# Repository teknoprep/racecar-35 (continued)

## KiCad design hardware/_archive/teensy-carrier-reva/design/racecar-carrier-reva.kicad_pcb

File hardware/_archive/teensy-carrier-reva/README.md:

# Racecar-35 Teensy carrier — Rev A prototype

**UNBUILT / NOT RELEASED FOR VEHICLE USE.** This is a complete, routed **prototype
carrier PCB**, not a validated automotive ECU and not a production safety sign-off.
Start with a small prototype order only after an electronics engineer reviews the
schematic, module orientations, connector pinouts, and protection scheme. Read
[BRINGUP.md](BRINGUP.md) before connecting a Teensy or display.

## What you get

- Editable **KiCad 9** project, hierarchical schematic and local libraries in `design/`.
- `schematic.pdf`: overview + four circuit/connectivity sheets.
- `BOM.csv`: per-reference manufacturer and part number; `BOM-grouped.csv`: grouped
  purchasing list (excludes bare-PCB test pads/mounting holes); `BOM-extra.csv`: sockets,
  mating connectors, harness fuse, standoffs and externally attached modules.
- `gerbers/`: two copper layers, solder masks, silkscreens, front paste, outline,
  plated/non-plated Excellon drill files and a drill map.
- `racecar-carrier-reva-GERBERS-PROTOTYPE.zip`: bare-PCB manufacturing files only.
- `assembly-positions.csv`, `assembly-top.pdf`, `board-top.png`, `board-bottom.png`.
- `reports/`: PCB DRC, limited schematic ERC, schematic/netlist cross-check and hashes.
- `export.sh`: fail-hard verification and export; does **not** regenerate or reroute.

A PCB fabricator needs the **Gerber ZIP plus FABRICATION.md**. Gerbers alone do not
specify copper weight. A PCB assembler additionally needs the BOM, positions, PDFs,
and hand-assembly notes. This is **not** a turnkey JLCPCB/LCSC assembly order: the
Teensy, Pololu and Traco modules, sockets and some connectors may require consignment
or hand assembly. Position-file rotations must be reviewed against the assembler's
package conventions. There is no claim that every MPN is currently stocked.

## Basic design and limits

| Item | Rev A |
|---|---|
| PCB | 130 × 110 mm; 2 layers; 1.6 mm FR4; **2 oz finished copper on BOTH sides** |
| Main input | **10–20 V DC**, common negative; not an unprotected battery connection |
| Main regulator U2 | **Pololu D36V50F5, product 4091**; published 5.5–50 V input, 5 V nominal, typical 5.5 A at 36 V; this carrier budgets **5 A total** on the main 5 V rail |
| Screen branch | 5 V output, **4 A fast fuse F2**; no adjustable output voltage |
| Auxiliary regulator U3 | **Traco TSR 1-2433**, 3.3 V, nominal 1 A; Rev A peripheral budget **500 mA combined** until thermal testing |
| MCU | Socketed **Teensy 4.1**, supplied at VIN through SS14 and JP1; never externally feed its 3.3 V pins |
| Screen link | Full-duplex **5 V TTL UART**, translated to Teensy's 3.3 V logic; 921600 baud firmware |
| Screen connector | Four-position 5.08 mm screw terminal, matching functions of Advance **J10** |
| Tach | External optocoupler output -> pull-up/filter/Schmitt buffer -> **Teensy 9** |
| GPS | Four-pin JST-XH custom UART connector, **3.3 V power and logic** |
| IMU | Four-pin JST-XH, 3.3 V, I²C on Teensy 18/19 |
| Optional CAN | Connector for an **external SN65HVD230 transceiver module**; not CANH/CANL |
| Optional Ethernet | Custom 2×4 header for a **3.3 V W5500 breakout**; not a plug-compatible W5500 footprint |

The regulator's published current is not a guarantee of **continuous 5 A in your
closed, hot trunk enclosure**. Verify at 10, 14.4 and 20 V, maximum brightness/radio
activity, and maximum intended ambient. Fuse values are not precise current limits.
The screen is not forced to draw 4 A or 5 A; it draws its own load current.
The screen fuse leaves margin for the MCU. U3 is fed separately from the protected
input, so its output is not drawn through the Teensy's small 3.3 V regulator.

This first PCB deliberately uses an **assembled regulator module** instead of a
new discrete 25 W buck-converter design. U2 mounts above the carrier on a soldered
2×6 header. That makes the power design easier to build and review; it is not the
cheapest possible mass-production implementation.

### Not included

GPS receiver/antenna, MPU-6050, CAN transceiver and W5500 are external modules.
There is **no** SMA connector or GNSS chip on this carrier: the SMA stays on the GPS
breakout, away from switching regulators. The Teensy's own SD slot is used. No raw
coil/ignition input, no direct 12 V tach, and **no oil-pressure/NTC conditioning** are
implemented. Firmware ADC readings must not be trusted without the existing proper
external conditioning; pins 16/17 are not brought to sensor screw terminals here.

There is no firmware change, GPS-module auto-detection, or M10/F10 library migration
in this PCB package. The current firmware's tested target remains NEO-M9N.
**A compatible UART voltage does not imply software compatibility with every u-blox
generation.** Verify the exact GPS board and library support before purchasing.

## Power protection — what it does and does not do

```
J1 +10–20V -> F1 5A -> VIN_FUSED -> U2 VIN -> U2 reverse protection -> buck -> +5V_MAIN
                          |                       |
                     SMBJ20CA D1             U2 VRP -> U3 -> +3V3_AUX
                          |                                       (GPS/IMU/modules)
                         GND
+5V_MAIN -> F2 4A -> +5V_SCREEN -> J2 pin 2 and UART cable-side supplies
+5V_MAIN -> D2 SS14 -> JP1 -> Teensy VIN
Teensy 3V3 -> +3V3_MCU -> low-current logic buffers only
```

- U2 includes reverse-input protection (published up to 40 V reverse), current/short
  protection and thermal shutdown. U3 takes **VRP**, after U2's reverse protection,
  not the unprotected input. U2's EN/PG are unused; VRP must not be confused with VIN.
- D1 is **SMBJ20CA, bidirectional**, after F1. Its 20 V standoff and approximately
  32.4 V clamp at rated pulse current fit the nominal 10–20 V design. This does NOT
  establish an automotive transient rating: pulse energy, source impedance, wiring
  inductance and actual clamp voltage matter. The Traco input max is 36 V.
- **Not qualified for ISO 7637 or ISO 16750 load dump, jump-start or cranking.** Use a
  properly protected vehicle DC feed. Add a real surge-stopper/automotive front-end
  after reviewing the vehicle supply requirements, before permanent installation.
- Fit an **external 5 A harness fuse near the battery/source**. F1 only protects
  downstream of this board's input; it cannot protect the cable before the PCB.
- **Fuses do not protect a GPIO against a 5 V/12 V mistake**, and neither a fuse nor
  a current-limited supply guarantees a semiconductor will survive a fault.
- D2 blocks USB-powered Teensy VIN from feeding back into the carrier 5 V bus. It
  does **not** block carrier power from entering the computer through an intact
  Teensy VUSB/VIN bridge. **CUT THAT BRIDGE before simultaneous USB/carrier power.**
- JP1 is an initial bring-up isolation jumper, not a hot-switching control. Do not
  energize external sensors while a connected Teensy is unpowered: GPIO protection
  paths or pull-ups can phantom-power it. Make all wiring changes with all power off.
- The two 3.3 V rails must remain separate. Do not bridge AUX 3V3 to Teensy 3V3.

## Connector pinout — top view, square pad is pin 1

The words RX/TX on the carrier refer to the **Teensy/carrier**, not the screen.
Do not guess orientation from wire colours or a vendor's cable plug.

### J1 — 10–20 V input, Phoenix MKDS 1,5/2-5,08

1. Positive input, 10–20 V.
2. GND / negative return.

### J2 — SCREEN, Phoenix MKDS 1,5/4-5,08

| Pin | Carrier function | Connect to CrowPanel Advance |
|---|---|---|
| 1 | GND | J10 GND |
| 2 | **+5 V OUTPUT**, fused 4 A | J10 **+5V_IN** |
| 3 | RX: receives screen data, 5 V side | J10 **TXD0_H** |
| 4 | TX: transmits to screen, 5 V side | J10 **RXD0_H** |

**Use the larger XH2.54 / J10 power-capable header on the genuine Advance. NEVER
connect pin 2 to the small HY2.0 / J2 `3V3_OUT` header.** A clone's connector labels,
pin order and circuitry must be checked against its schematic and measured with a
meter first; its USB identity cannot establish its power-header pinout. Do not use
a same-looking cable without a pin-to-pin continuity test.

U4 is SN74LVC1T45: A=3.3 V Teensy TX, B=5 V cable TX, DIR high.
U5 reverses direction: B=5 V cable RX, A=3.3 V Teensy RX, DIR low.
Both support power-off isolation; their cable-side supply is after the screen fuse.
100 Ω series resistors and PESD5V0S1BA ESD clamps are fitted at the cable paths.
They are **not RS-232 converters** and not a 12 V miswire-protection system.

### J3 — external optocoupler, two-position screw terminal

1. GND, optocoupler output-side emitter/ground.
2. Optocoupler collector/output signal; goes to **Teensy pin 9 through U6**.

Default: **open collector**, with R6 4.7 kΩ pull-up to MCU 3.3 V. R5=1 kΩ and
C11=1 nF form a small input filter; U6 gives a 3.3 V Schmitt output. No extra onboard
opto is included. For a verified push-pull 3.3/5 V source, review/remove R6 so the
external source cannot feed the MCU supply through the pull-up, especially when
the carrier is off. Do not connect an independently powered tach module without
checking its output topology. Never attach a coil or 12 V tach signal directly.

### J4 — GPS, JST B4B-XH-A (2.50 mm)

1. +3V3_AUX **output**.
2. GND.
3. Carrier TX (Teensy 8, via R8) -> GPS RX.
4. Carrier RX (U6 input, Teensy 7) <- GPS TX.

This is a **custom harness**, not a GPS vendor standard. Choose a breakout whose
specified supply pin accepts 3.3 V. A board that requires 5 V into an onboard
regulator is not powered correctly by blindly connecting J4 pin 1 to its VIN.
Do not connect USB to the GPS while it is powered/connected here unless its vendor
explicitly permits those supply combinations and its USB-UART interface is isolated.
GPS firmware configuration and antenna requirements remain module-specific.

### J5 — IMU, JST-XH

1. +3V3_AUX; 2. GND; 3. SDA (Teensy 18); 4. SCL (Teensy 19).
MPU-6050 AD0 -> GND. R12/R13 are 4.7 kΩ I²C pull-ups; account for parallel pull-ups
already on the breakout. Keep I²C wires short. Do not allow pull-ups to 5 V.

### J6 — CAN transceiver module LOGIC, JST-XH

1. +3V3_AUX; 2. GND; 3. Teensy 22 TX -> module CTX/D; 4. Teensy 23 RX <- module CRX/R.
Use a 3.3 V **SN65HVD230** module. CANH/CANL are on that external module, not J6.
CAN termination: only at the two physical bus ends; include existing module resistors
when checking resistance. A powered-off correctly terminated bus is typically ~60 Ω
across CANH/CANL. No transceiver or terminator is fitted on this carrier.

### J7 — optional W5500, 2×4, 2.54 mm

| Pin | Function | Pin | Function |
|---|---|---|---|
| 1 | +3V3_AUX | 2 | GND |
| 3 | CS, Teensy 10 | 4 | MOSI, Teensy 11 |
| 5 | MISO, Teensy 12 | 6 | SCK, Teensy 13 |
| 7 | RESET, Teensy 6 | 8 | INT, Teensy 5 |

Custom wiring only; most W5500 modules have a different pin order. Must be powered
from 3.3 V at the specified input and use 3.3 V I/O. R10 pulls CS high and R11 pulls
RESET high. INT/RESET are wired for future use; current firmware does not promise
those optional GPIO functions are implemented. Keep SPI short and bench-test at
the firmware's clock rate. All external module current counts against the AUX budget.

## Cable reality

A four-terminal connector does not make trunk-length TTL UART noise-immune.
**Rev A has not been verified across the car at 921600 baud.** Test under engine,
alternator and radio activity with error/retry counts and a scope. If it is not
reliable, use differential transceivers at **both ends**; that needs a screen-side
adapter and potentially protocol/wiring changes, not just a different cable.

For power, calculate the **round-trip** drop. Example at 3 m one-way / 4 A:
- 18 AWG copper: approximately 0.50 V drop before connectors/fuses/temperature.
- 16 AWG: approximately 0.32 V.
- 14 AWG: approximately 0.20 V.

Select wire by measured screen current and allowable drop; don't assume a thin
four-core serial cable can carry 4–5 A. The screen's input diode adds more loss.
Use strain relief and ferrules compatible with the screw terminals, not loose
solder-tinned stranded wire under screws. A harness can have heavy power conductors
plus separately shielded/twisted signal/ground pairs while terminating at four
functions. Do not tie a shield to positive power. For now, begin with short bench
wires and measure voltage **at the screen** at maximum load.

## Verification performed and limits

`export.sh` requires:
1. KiCad PCB DRC: **zero violations, zero unconnected items**.
2. Schematic ERC: no violations. **Symbols are pin-labelled passive connectivity
   blocks**, so this ERC does not verify driver conflicts, supply sequencing or
   semiconductor voltage/current limits. Do not treat it as full electrical validation.
3. Independent assertions for key pin maps, power separation, polarity and fixed
   translator direction. Exported schematic netlist must match all 161 connected
   PCB pads from `components.json`.
4. Wide manually routed power trunks survive routing. No high-current trunk uses
   a single signal via. Ground uses wide back-layer trunks and pours on both sides.

Not done: independent engineer review, physical footprint fit, board fabrication,
measured regulator startup/ripple/fault response, thermal load testing, sustained
5 A testing, EMI, automotive transients, enclosure fit or long-cable UART tests.
These are release blockers for permanent vehicle use. Current capability cannot be
proven by Gerbers or DRC alone. Replacement modules must match the exact footprints.

## Rebuilding / editing

Tools used: KiCad 9.0.8, Python `pcbnew` from the system KiCad package, Freerouting
1.9.0 / Java 17 (under Xvfb), and CairoSVG for previews. Libraries are project-local.
Firmware builds, binaries and frozen OTA bridge are untouched.

**`generate.py` overwrites the routed PCB.** To intentionally regenerate:

```sh
/usr/bin/python3 generate.py
/usr/bin/python3 schematic.py
# Run in a scratch directory so Freerouting logs don't enter the repo:
xvfb-run -a java -jar /path/to/freerouting-1.9.0.jar \
  -de /absolute/path/design/racecar-carrier-reva.dsn \
  -do /absolute/path/design/racecar-carrier-reva.ses -mp 12 -mt 1 -da
/usr/bin/python3 finish_board.py
./export.sh
```

Delete the prior `.ses` before a new routing run so failure cannot reuse stale routes.
Source and routed `.dsn/.ses` are retained. Alternatively edit the final KiCad files
in the GUI, then update the generated source/manifest or stop using generation; never
silently overwrite manual edits. `export.sh` exports the existing final board only.

## Reference sources

- PJRC Teensy 4.1 pinout: https://www.pjrc.com/teensy/card11a_rev4_web.pdf
- Pololu module, current curves and connection diagrams: https://www.pololu.com/product/4091
- Traco TSR 1 datasheet: https://www.tracopower.com/products/tsr1.pdf
- TI translator: https://www.ti.com/lit/ds/symlink/sn74lvc1t45.pdf
- TI Schmitt buffer: https://www.ti.com/lit/ds/symlink/sn74lvc2g17.pdf
- `references/` contains the retrieved PJRC card and Pololu diagrams. Pololu's
  dimension picture is a **BOTTOM** view; the labelled power-pin picture is **TOP**.
- Stock footprint geometry: KiCad 9 footprint library, copied into `design/Racecar.pretty`.

Manufacturer documents govern. Some supplier sites could not be fetched from this
host; part selection and the current stock library are not a substitute for reviewing
the latest purchased-part datasheets before placement of an assembly order.

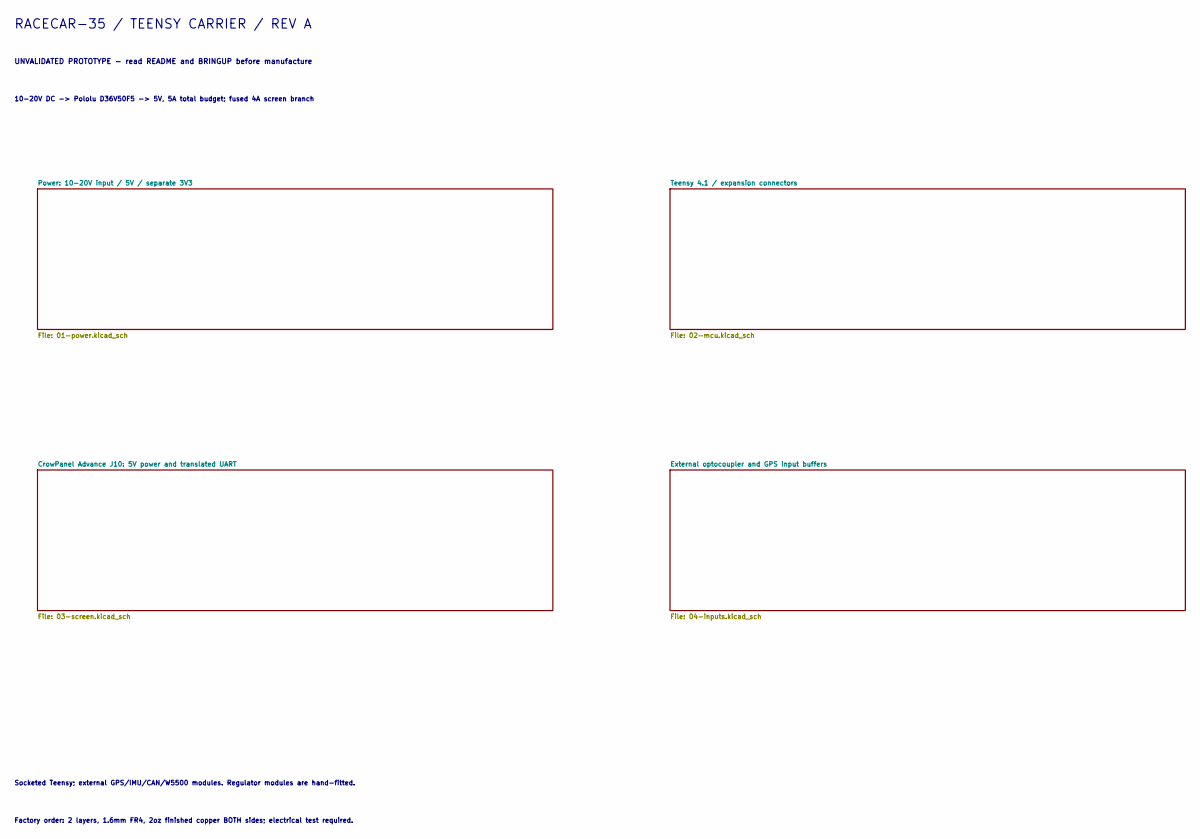
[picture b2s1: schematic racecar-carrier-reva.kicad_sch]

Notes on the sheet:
RACECAR-35 / TEENSY CARRIER / REV A
UNVALIDATED PROTOTYPE - read README and BRINGUP before manufacture
10-20V DC -> Pololu D36V50F5 -> 5V, 5A total budget; fused 4A screen branch
Socketed Teensy; external GPS/IMU/CAN/W5500 modules. Regulator modules are hand-fitted.
Factory order: 2 layers, 1.6mm FR4, 2oz finished copper BOTH sides; electrical test required.

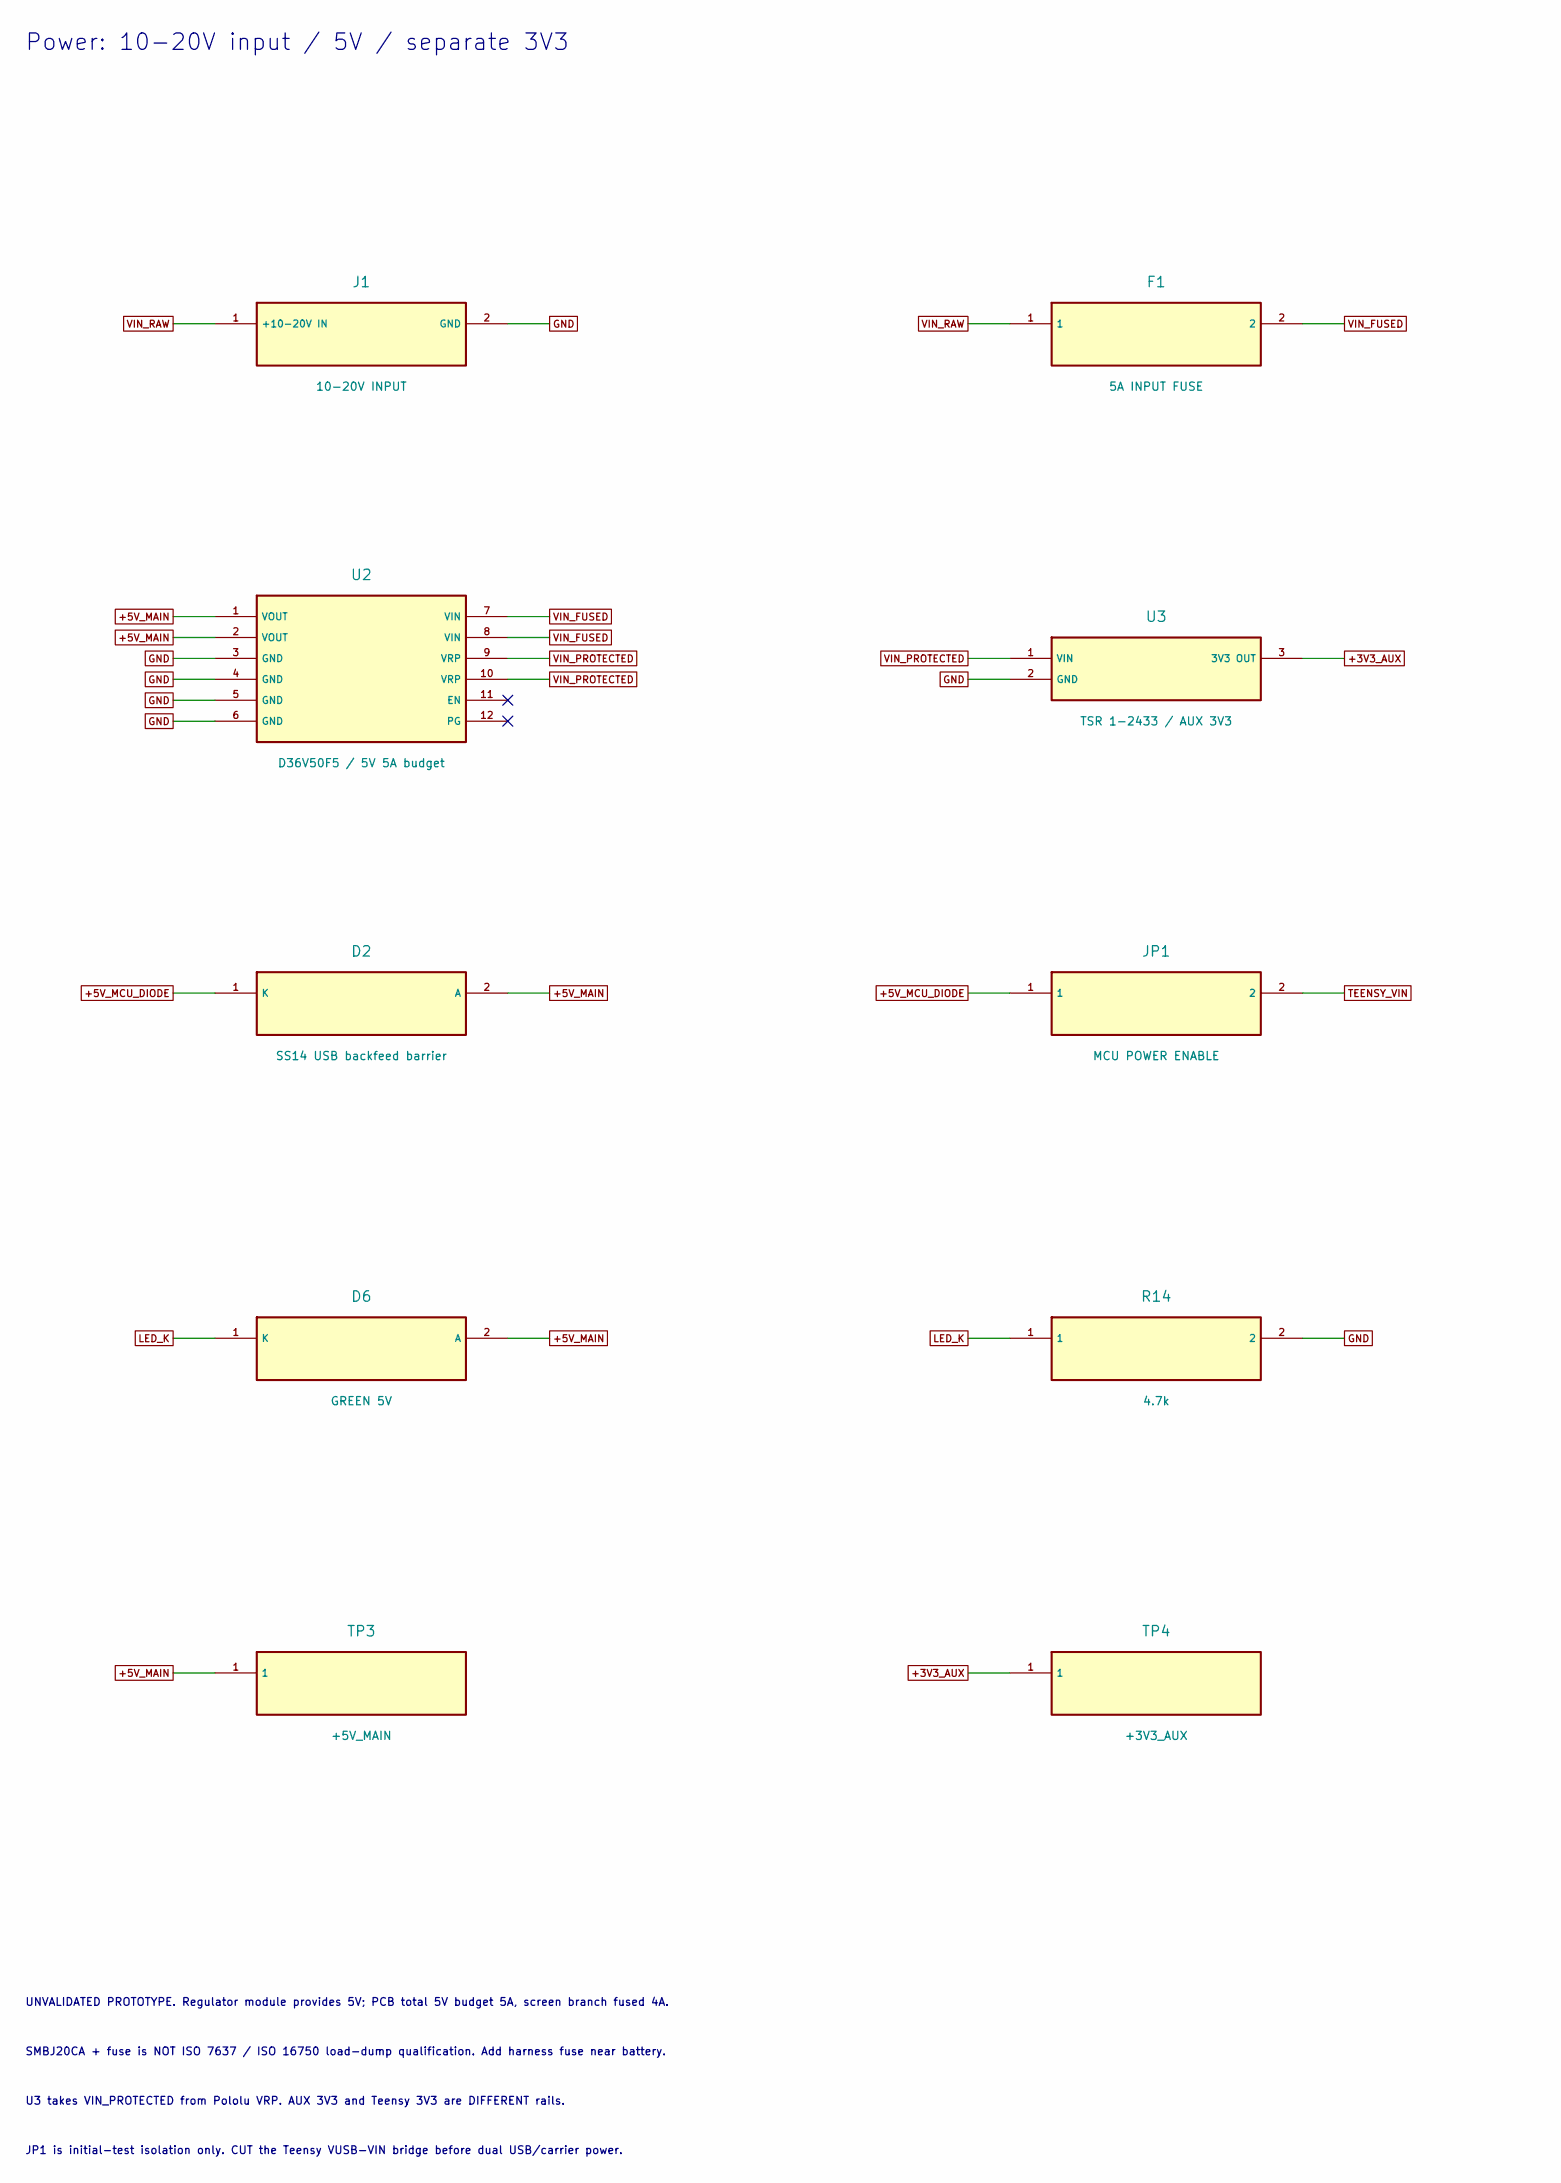
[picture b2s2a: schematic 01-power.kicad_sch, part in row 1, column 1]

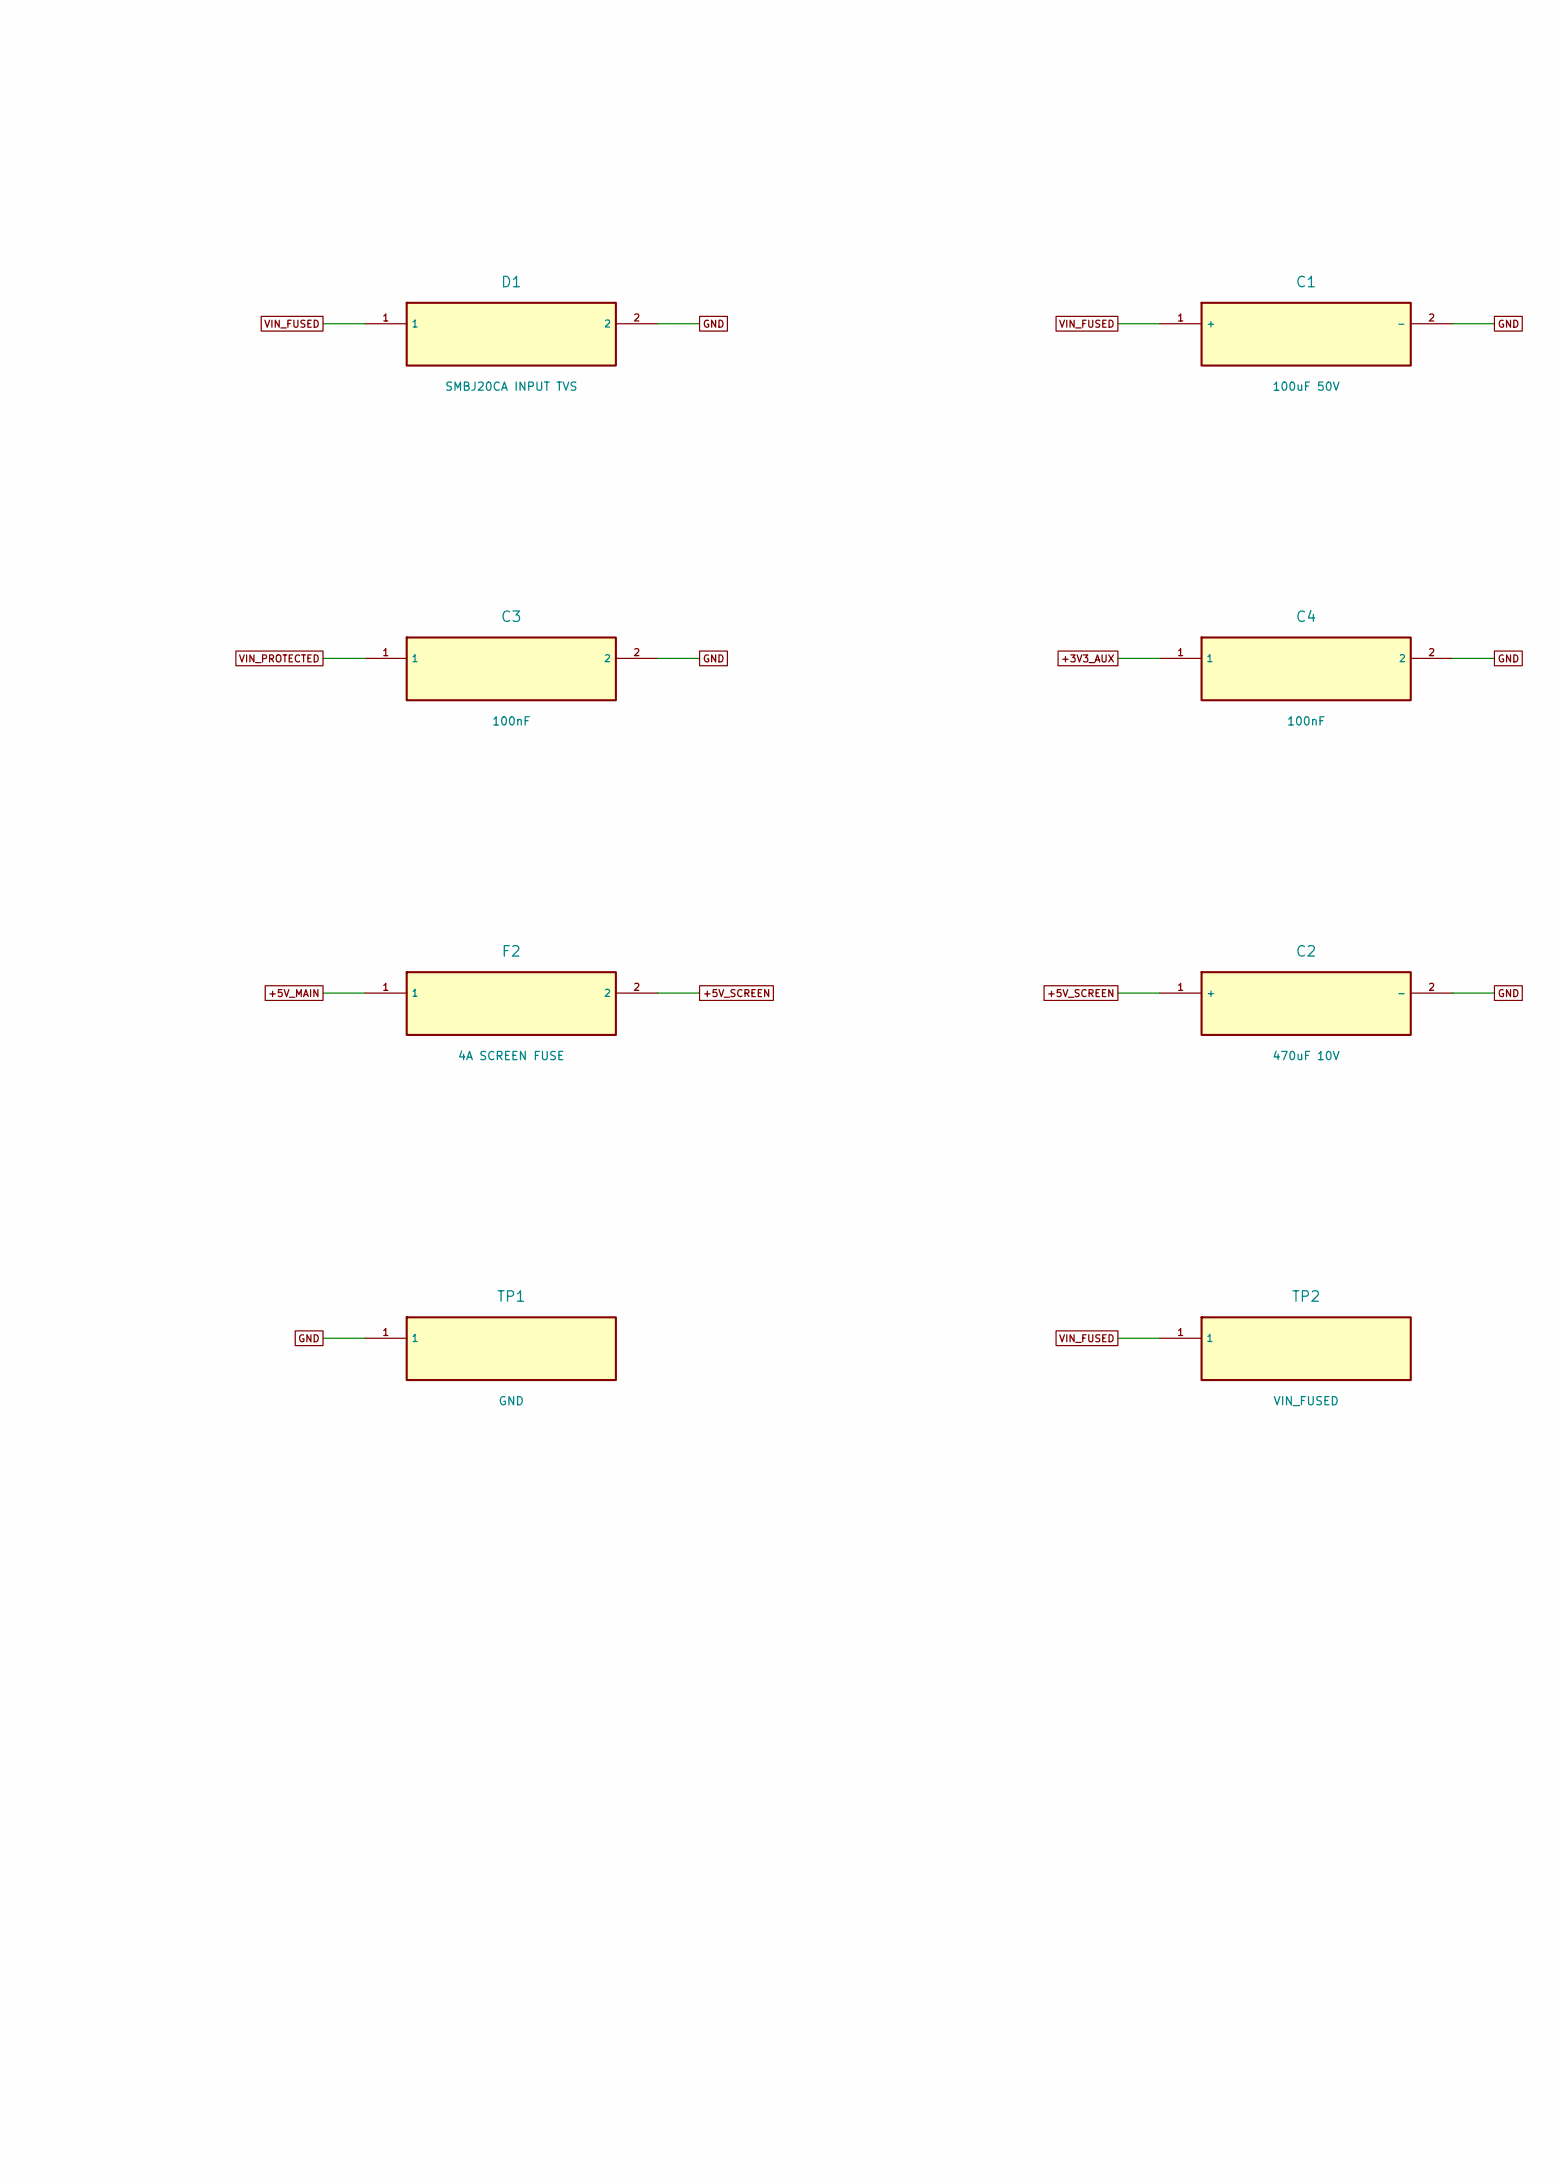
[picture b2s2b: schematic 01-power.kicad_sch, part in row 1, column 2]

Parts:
C1: 100uF 50V; CP_Radial_D8.0mm_P3.50mm
C2: 470uF 10V; CP_Radial_D8.0mm_P3.50mm
C3, C4: 100nF; C_0805_2012Metric_Pad1.18x1.45mm_HandSolder
D1: SMBJ20CA INPUT TVS; D_SMB
D2: SS14 USB backfeed barrier; D_SMA
D6: GREEN 5V; LED_0805_2012Metric
F1: 5A INPUT FUSE; Fuse_Littelfuse-NANO2-451_453
F2: 4A SCREEN FUSE; Fuse_Littelfuse-NANO2-451_453
J1: 10-20V INPUT; TerminalBlock_Phoenix_MKDS-1,5-2-5.08_1x02_P5.08mm_Horizont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
JP1: MCU POWER ENABLE; PinHeader_1x02_P2.54mm_Vertical
R14: 4.7k; R_0805_2012Metric_Pad1.20x1.40mm_HandSolder
TP1: GND; TestPoint_THTPad_D2.0mm_Drill1.0mm
TP2: VIN_FUSED; TestPoint_THTPad_D2.0mm_Drill1.0mm
TP3: +5V_MAIN; TestPoint_THTPad_D2.0mm_Drill1.0mm
TP4: +3V3_AUX; TestPoint_THTPad_D2.0mm_Drill1.0mm
U2: D36V50F5 / 5V 5A budget; Pololu_D36V50F5
U3: TSR 1-2433 / AUX 3V3; Converter_DCDC_TRACO_TSR-1_THT

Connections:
+3V3_AUX: C4.1, TP4.1, U3.3 (3V3 OUT); also elsewhere on the board
+5V_MAIN: D2.2 (A), D6.2 (A), F2.1, TP3.1, U2.1 (VOUT), U2.2 (VOUT)
+5V_MCU_DIODE: D2.1 (K), JP1.1
+5V_SCREEN: C2.1 (+), F2.2; also elsewhere on the board
GND: C1.2 (-), C2.2 (-), C3.2, C4.2, D1.2, J1.2 (GND), R14.2, TP1.1, U2.3 (GND), U2.4 (GND), U2.5 (GND), U2.6 (GND), U3.2 (GND); also elsewhere on the board
LED_K: D6.1 (K), R14.1
TEENSY_VIN: JP1.2; also elsewhere on the board
VIN_FUSED: C1.1 (+), D1.1, F1.2, TP2.1, U2.7 (VIN), U2.8 (VIN)
VIN_PROTECTED: C3.1, U2.9 (VRP), U2.10 (VRP), U3.1 (VIN)
VIN_RAW: F1.1, J1.1 (+10-20V IN)

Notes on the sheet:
Power: 10-20V input / 5V / separate 3V3
UNVALIDATED PROTOTYPE. Regulator module provides 5V; PCB total 5V budget 5A, screen branch fused 4A.
SMBJ20CA + fuse is NOT ISO 7637 / ISO 16750 load-dump qualification. Add harness fuse near battery.
U3 takes VIN_PROTECTED from Pololu VRP. AUX 3V3 and Teensy 3V3 are DIFFERENT rails.
JP1 is initial-test isolation only. CUT the Teensy VUSB-VIN bridge before dual USB/carrier power.

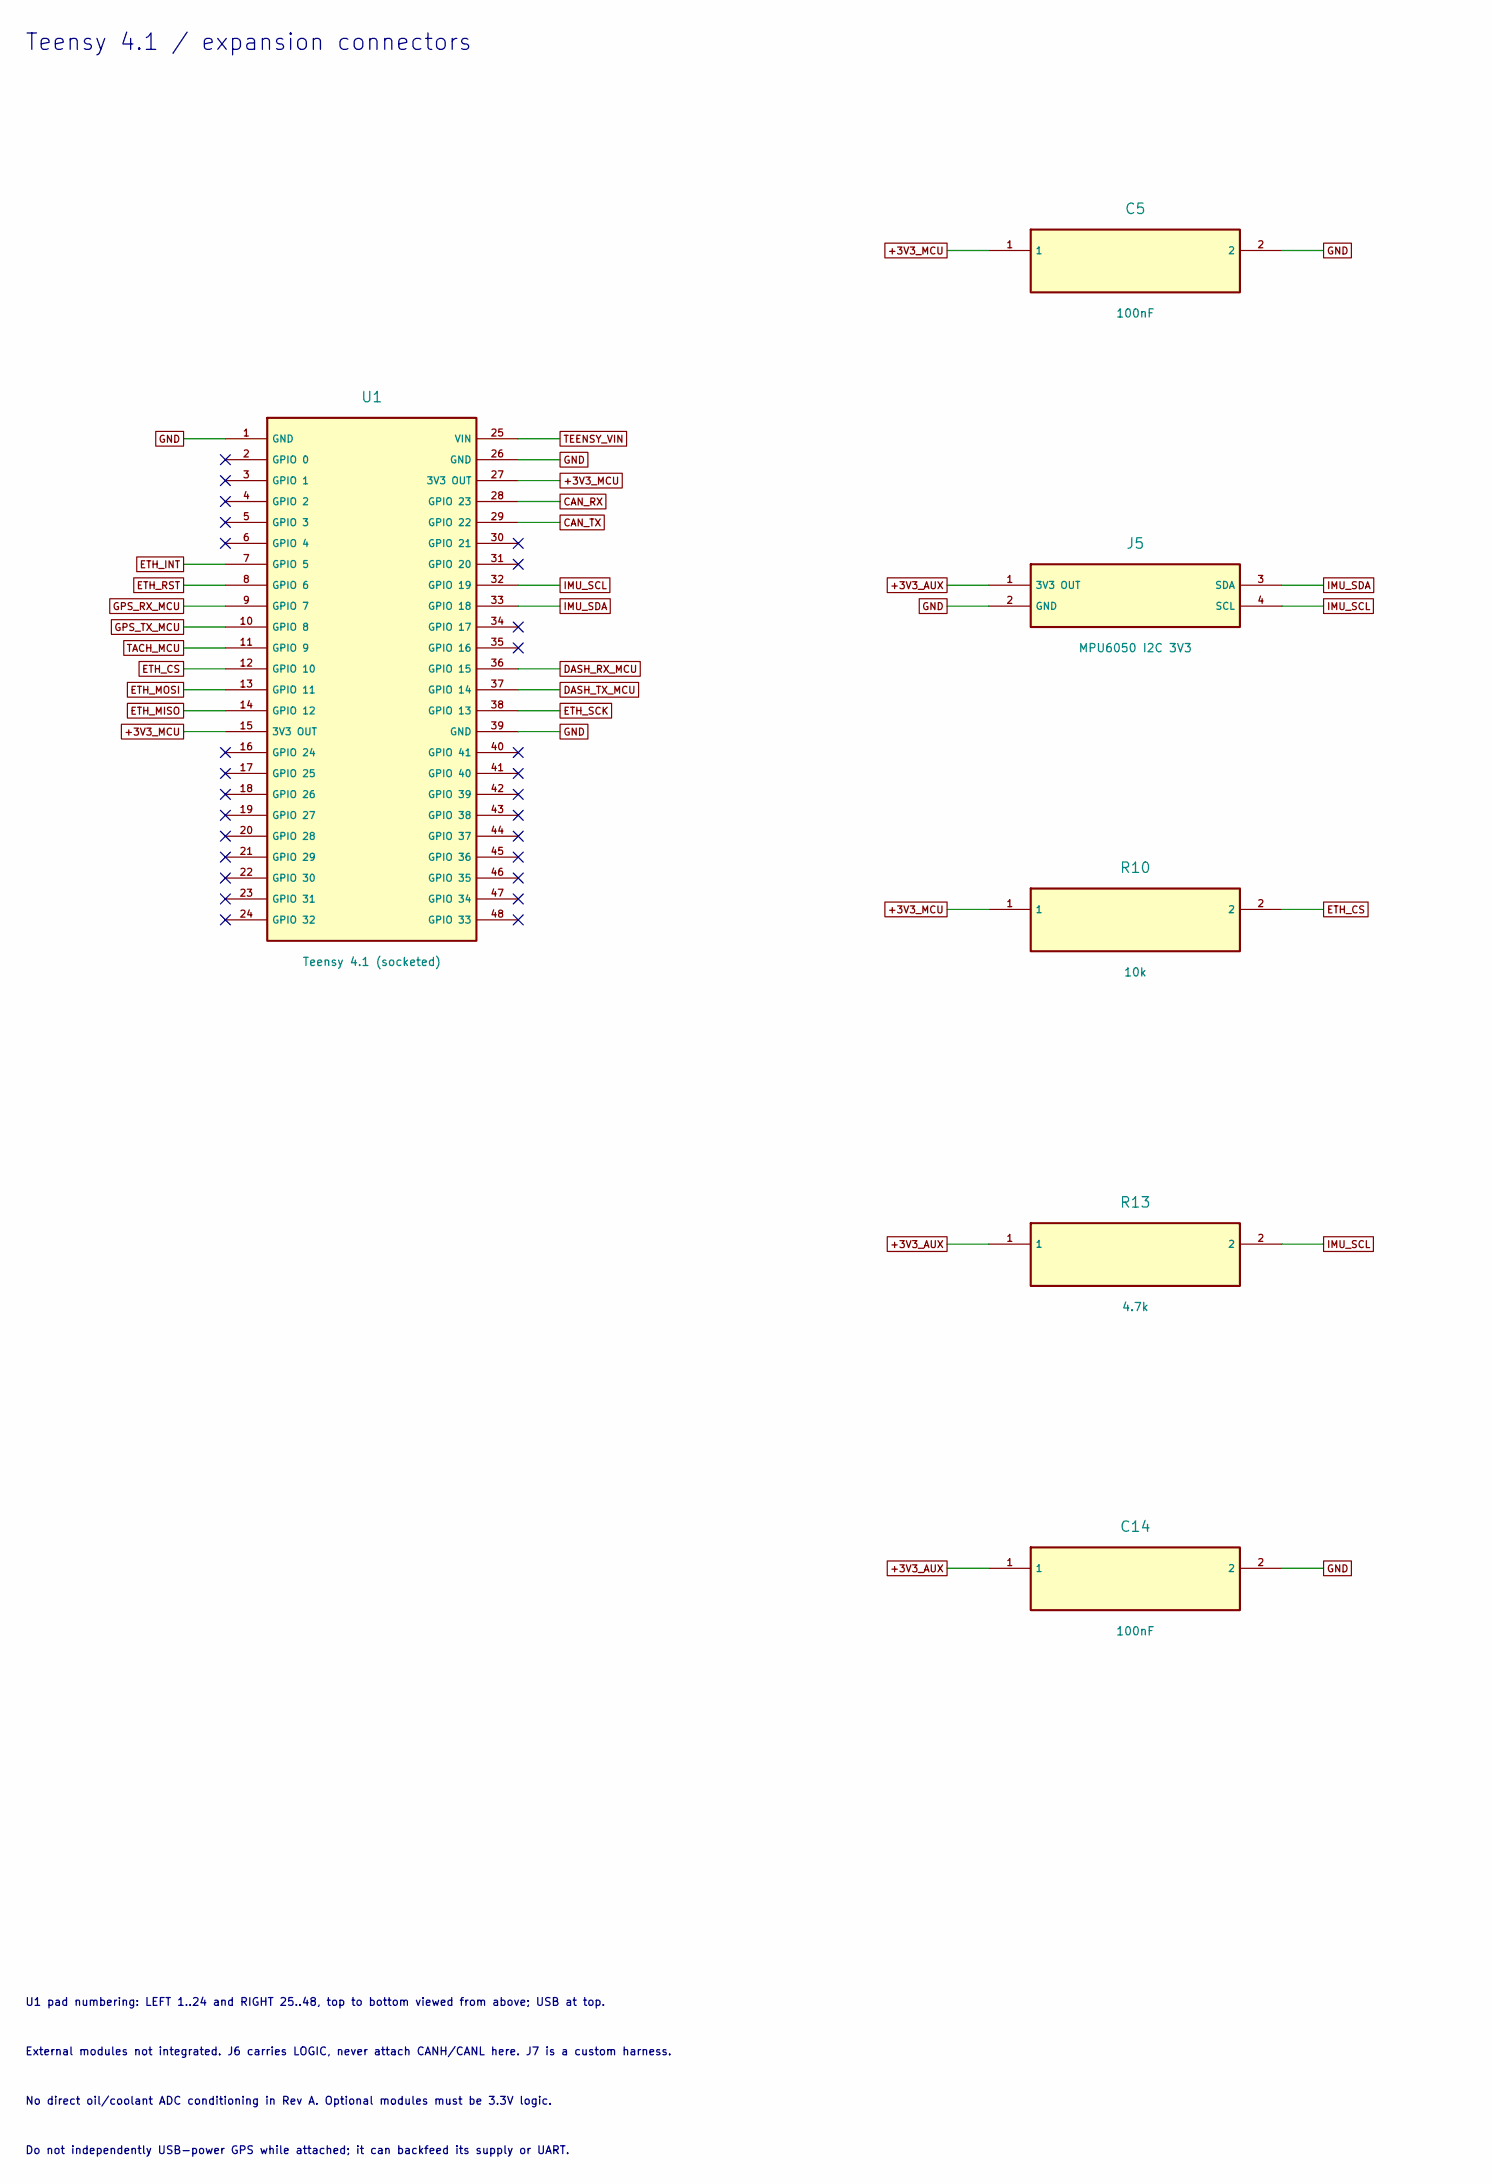
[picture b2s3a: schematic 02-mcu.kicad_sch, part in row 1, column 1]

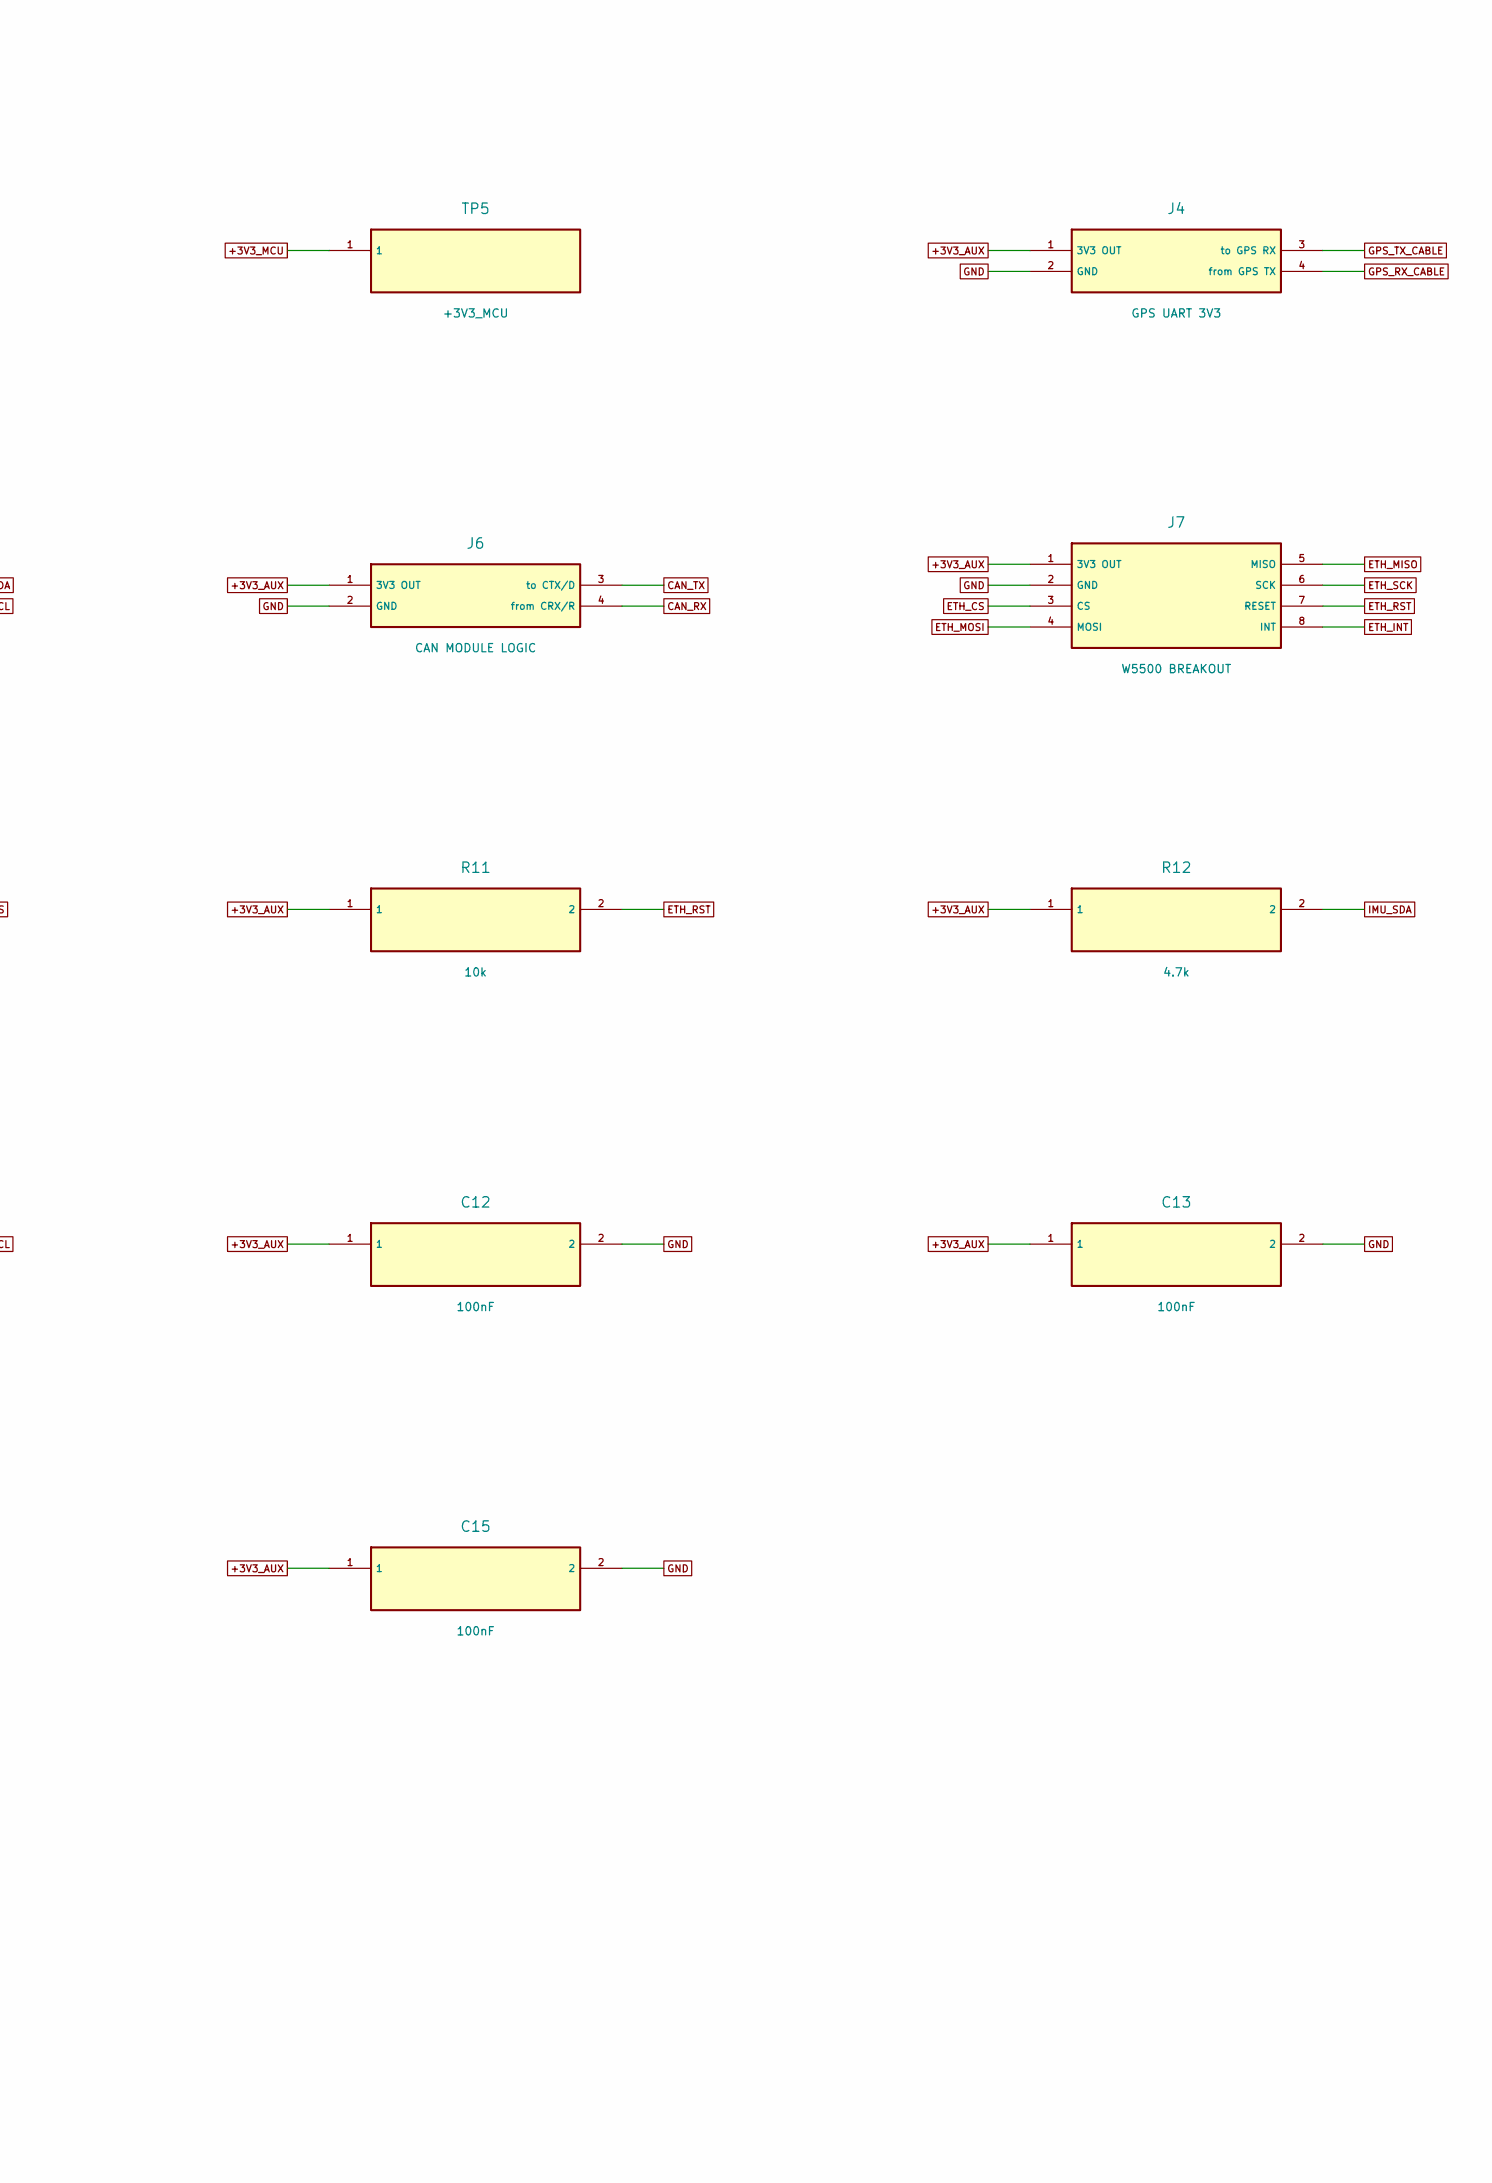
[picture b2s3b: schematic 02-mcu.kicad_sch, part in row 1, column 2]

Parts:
C5, C12, C13, C14, C15: 100nF; C_0805_2012Metric_Pad1.18x1.45mm_HandSolder
J4: GPS UART 3V3; JST_XH_B4B-XH-A_1x04_P2.50mm_Vertical
J5: MPU6050 I2C 3V3; JST_XH_B4B-XH-A_1x04_P2.50mm_Vertical
J6: CAN MODULE LOGIC; JST_XH_B4B-XH-A_1x04_P2.50mm_Vertical
J7: W5500 BREAKOUT; PinHeader_2x04_P2.54mm_Vertical
R10, R11: 10k; R_0805_2012Metric_Pad1.20x1.40mm_HandSolder
R12, R13: 4.7k; R_0805_2012Metric_Pad1.20x1.40mm_HandSolder
TP5: +3V3_MCU; TestPoint_THTPad_D2.0mm_Drill1.0mm
U1: Teensy 4.1 (socketed); Teensy41_Socket

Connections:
+3V3_AUX: C12.1, C13.1, C14.1, C15.1, J4.1 (3V3 OUT), J5.1 (3V3 OUT), J6.1 (3V3 OUT), J7.1 (3V3 OUT), R11.1, R12.1, R13.1; also elsewhere on the board
+3V3_MCU: C5.1, R10.1, TP5.1, U1.15 (3V3 OUT), U1.27 (3V3 OUT); also elsewhere on the board
CAN_RX: J6.4 (from CRX/R), U1.28 (GPIO 23)
CAN_TX: J6.3 (to CTX/D), U1.29 (GPIO 22)
DASH_RX_MCU: U1.36 (GPIO 15); also elsewhere on the board
DASH_TX_MCU: U1.37 (GPIO 14); also elsewhere on the board
ETH_CS: J7.3 (CS), R10.2, U1.12 (GPIO 10)
ETH_INT: J7.8 (INT), U1.7 (GPIO 5)
ETH_MISO: J7.5 (MISO), U1.14 (GPIO 12)
ETH_MOSI: J7.4 (MOSI), U1.13 (GPIO 11)
ETH_RST: J7.7 (RESET), R11.2, U1.8 (GPIO 6)
ETH_SCK: J7.6 (SCK), U1.38 (GPIO 13)
GND: C5.2, C12.2, C13.2, C14.2, C15.2, J4.2 (GND), J5.2 (GND), J6.2 (GND), J7.2 (GND), U1.1 (GND), U1.26 (GND), U1.39 (GND); also elsewhere on the board
GPS_RX_CABLE: J4.4 (from GPS TX); also elsewhere on the board
GPS_RX_MCU: U1.9 (GPIO 7); also elsewhere on the board
GPS_TX_CABLE: J4.3 (to GPS RX); also elsewhere on the board
GPS_TX_MCU: U1.10 (GPIO 8); also elsewhere on the board
IMU_SCL: J5.4 (SCL), R13.2, U1.32 (GPIO 19)
IMU_SDA: J5.3 (SDA), R12.2, U1.33 (GPIO 18)
TACH_MCU: U1.11 (GPIO 9); also elsewhere on the board
TEENSY_VIN: U1.25 (VIN); also elsewhere on the board

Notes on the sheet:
Teensy 4.1 / expansion connectors
U1 pad numbering: LEFT 1..24 and RIGHT 25..48, top to bottom viewed from above; USB at top.
External modules not integrated. J6 carries LOGIC, never attach CANH/CANL here. J7 is a custom harness.
No direct oil/coolant ADC conditioning in Rev A. Optional modules must be 3.3V logic.
Do not independently USB-power GPS while attached; it can backfeed its supply or UART.
